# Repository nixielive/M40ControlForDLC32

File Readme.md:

# Relay control board for M40 CO2 laser cutter power supply

This repository is a KiCad project for a relay control board that controls power supplies for laser cutters (such as M40) with TTL signals like MKS-DLC32.

# About the M40 Power Supply and MKS-DLC32

For details about the power supply for CO2 laser cutters and the CNC control MKS-DLC32, please refer to the information below.

|Item|Link|
|---|---|
|Laser Power Supply (M40)|[AliExpress](https://ja.aliexpress.com/item/32805183446.html?pdp_npi=4%40pre%21JPY%21￥%2011%2C993%21%21￥%208%2C155%21%2175.00%2157.00%21%402140d3ff17145295176637734ee02b%2164707149625%21sh%21JP%212424227286%21&spm=a2g0o.store_pc_allItems_or_groupList.new_all_items_2007447399652.32805183446&gatewayAdapt=glo2jpn)|
|MKS-DLC32 CNC Controller|[Github](https://github.com/makerbase-mks/MKS-DLC32)<br/>[AliExpress](https://ja.aliexpress.com/item/4000828878233.html?spm=a2g0o.order_list.order_list_main.53.1305585aAJdBHK&gatewayAdapt=glo2jpn)|

# About the circuit board created in this project

Reading the description of the M40 power supply, it says that the laser can be controlled ON/OFF based on the voltage level given to P2-L.

| Terminal | Pin | Description|
|---|-----|---------------------------------------------------------------------|
| P2 |  G   | Ground: The foot must connected with laser machine's enclosure and ground properly.|
| P2 |  P   | Water-Protection Switch|
| P2 |  <span style="color: red;">L</span>   | <span style="color: red;">Switch Laser Control: <br/>High Level (>3V) - Laser OFF; <br/>Low Level (≤0.3V) - Laser On.</span>|
| P2 |  G   | Ground: The foot must connected with laser machine's enclosure and ground properly.|
| P2 |  IN   | 0-5V Analog signal control input, also can use 5V PWM signal to control.|
| P2 |  5V   | Output 5V, Max Current 50mA.|

Based on this, it would seem that connecting the MKS-DLC32's TTL-Signal to P2-L should work, but this method did not succeed.

There is a good product for simply testing the M40, and this was used as a reference for designing this board.

[AliExpress - Power Supply Controller](https://ja.aliexpress.com/item/32944454101.html?spm=a2g0o.order_list.order_list_main.10.4671585aD0iIoW&gatewayAdapt=glo2jpn)

In this product, the laser can be turned ON by connecting P2-P to P2-L.

The short-circuit between P2-P and P2-L can be achieved using a Opto-isolator or MOSFET. In this project, the connection between P2-P and P2-L is switched with the MKS-DLC32's TTL signal using an N-ch MOSFET, the [BSS138](https://www.onsemi.com/pdf/datasheet/bss138-d.pdf).

The connections between the BSS138 and other modules are as follows:

|BSS138|Destination|
|---|---|
|Gate(1)|DLC32-TTL(Laser Control)|
|Source(2)|M40-P2-L / DLC-32-S|
|Drain(3)|M40-P2-P|

# How to Use the Project

Please open LaserControlConnector.kicad_pro in KiCad.

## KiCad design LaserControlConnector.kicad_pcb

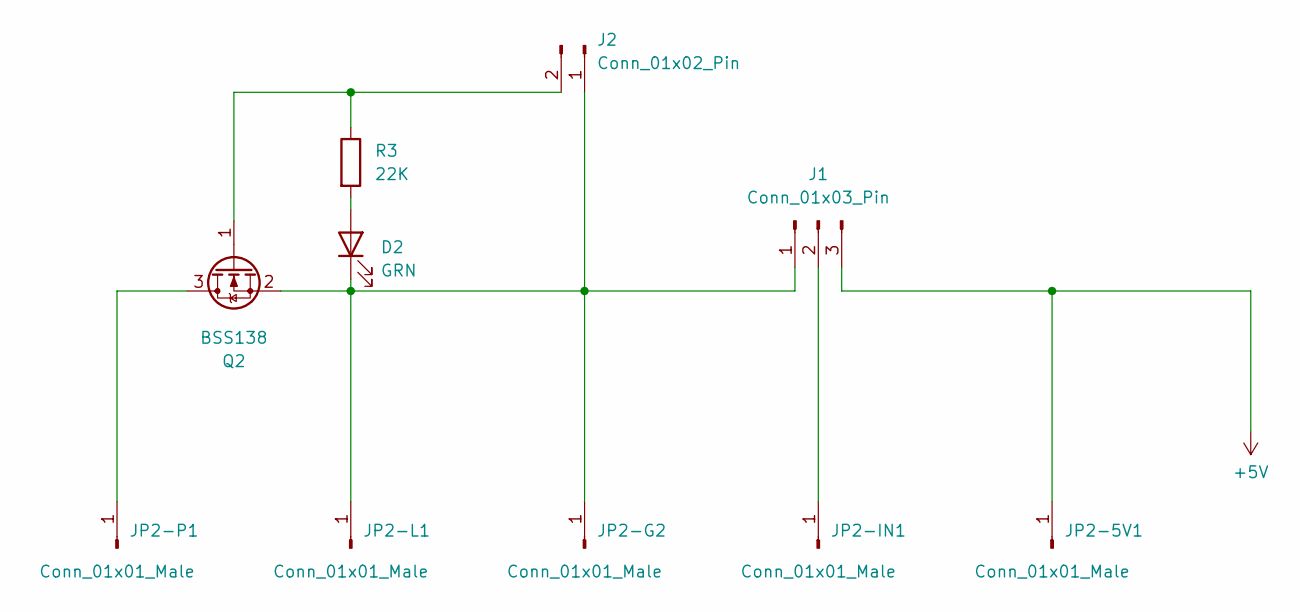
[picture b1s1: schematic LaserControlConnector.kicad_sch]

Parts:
D2: GRN; LED_D3.0mm
J1: Conn_01x03_Pin; JST_XH_B3B-XH-AM_1x03_P2.50mm_Vertical
J2: Conn_01x02_Pin; JST_XH_B2B-XH-A_1x02_P2.50mm_Vertical
JP2-5V1, JP2-G2, JP2-IN1, JP2-L1, JP2-P1: Conn_01x01_Male; Connector_Teeth
Q2: BSS138; SOT-23
R3: 22K; R_Axial_DIN0204_L3.6mm_D1.6mm_P5.08mm_Horizontal

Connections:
+5V: J1.3, JP2-5V1.1
unnamed: D2.2 (A), R3.2
unnamed: D2.1 (K), J1.1, J2.1, JP2-G2.1, JP2-L1.1, Q2.2 (S)
unnamed: J1.2, JP2-IN1.1
unnamed: J2.2, Q2.1 (G), R3.1
unnamed: JP2-P1.1, Q2.3 (D)

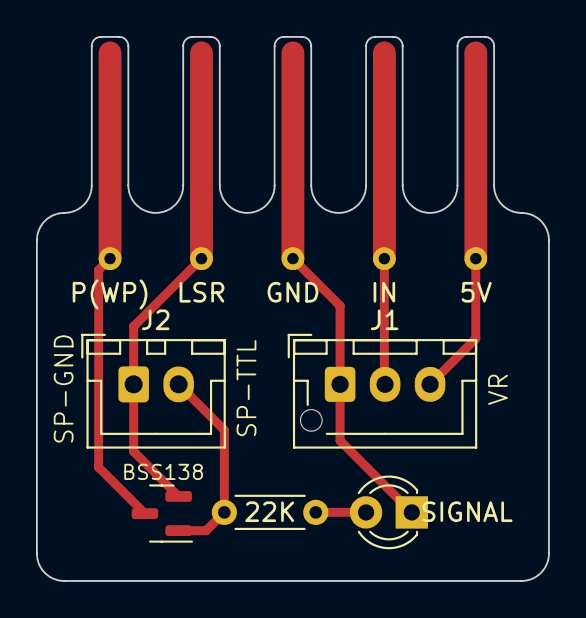
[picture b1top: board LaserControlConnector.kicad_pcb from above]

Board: 2 copper layers, 28.4 x 30.2 mm, 10 parts (0 on the bottom side), 6 nets.

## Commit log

2024-05-01 Init
